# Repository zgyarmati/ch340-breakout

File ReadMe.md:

This a simple CH340G breakout board design, for using (mainly) on breadboards. There are a dozen of good designs out 
there, but this one tries to differentiate itself by being breadboard-friendly (meaning it’s possible to plug it into 
your board without sticking out vertically), provides (fused) power supply directly to the power rails of the breadboard 
(selectable 5V or 3V3), and it exposes all of the modem control lines.

 I decided to design this when I was starting prototyping an other project, and wished I had something similar. After a 
 quick, unsuccessful query on Tindie (this is something similar, but not designed for breadboard, and not OSHW), the 
 next thing I noticed was that I have Kicad open and I’m laying out this board. It’s nothing groundbreaking, but as you 
 can see on the pictures, it’s directly pluggable into breadboard, and it can also power your breadboard circuit from 
 the USB port, so I’m sure it can come handy sometimes to everyone on Earth. The schematic is pretty much the default 
 design for the CH340G chip, plus there is some ESD protection on the USB line (USBLC6-2SC6), a 3.3V regulator with 
 jumpers to select the output VCC and the UART line voltage and of course some LEDs for power and the TX/RX lines, as 
 blinking LEDs are mandatory for any reasonable gadget.

The PCB is designed with Kicad, it’s double sided, but possible to build it on single-sided board as well. You can find 
all of the CAD files in this repo, but  here is a teaser:

The usage it’s pretty straightforward: just plug it into your breadboard, connect the UART lines to your circuit, select 
the operating voltage, and connect the USB cable to your PC. If you are using any {r,d}ecent Linux distribution, the 
CH340G driver most likely is installed on your machine. If you are on Windows, you have to click around a bit, see for 
example the tutorial at Sparkfun 

Bookmarks
---------

http://nicecircuits.com/ch340g-usb-to-rs232-ttl-module-schematic-d-sun-v3-0/

https://www.tindie.com/products/bitluni/cam-prog/?utm_source=hackaday&utm_medium=link&utm_campaign=fromstore#specs

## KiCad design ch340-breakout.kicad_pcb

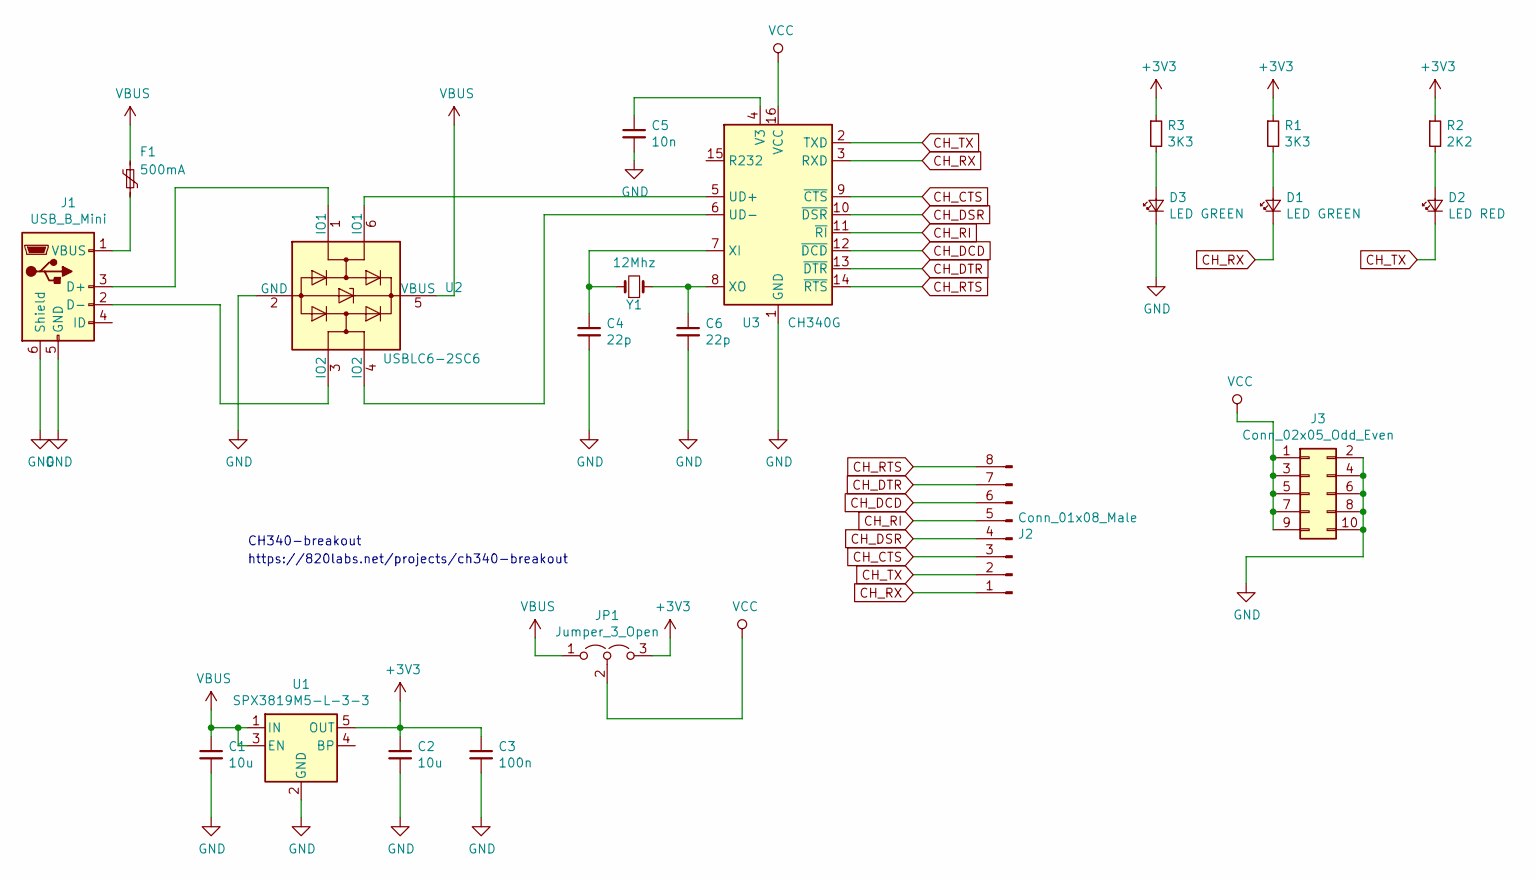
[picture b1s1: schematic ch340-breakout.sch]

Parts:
C1, C2: 10u; C_0805_2012Metric
C3: 100n; C_0805_2012Metric
C4, C6: 22p; C_0805_2012Metric
C5: 10n; C_0805_2012Metric
D1, D3: LED GREEN; LED_0805_2012Metric
D2: LED RED; LED_0805_2012Metric
F1: 500mA; Fuse_0805_2012Metric
J1: USB_B_Mini; USB_Mini-B_Lumberg_2486_01_Horizontal
J2: Conn_01x08_Male; PinHeader_1x08_P2.54mm_Vertical
J3: Conn_02x05_Odd_Even; PinHeader_2x05_P2.54mm_Vertical
JP1: Jumper_3_Open; PinHeader_1x03_P2.54mm_Vertical
R1, R3: 3K3; R_0805_2012Metric
R2: 2K2; R_0805_2012Metric
U1: SPX3819M5-L-3-3; SOT-23-5
U2: USBLC6-2SC6; SOT-23-6
U3: CH340G; SOIC-16_3.9x9.9mm_P1.27mm
Y1: 12Mhz; Crystal_SMD_HC49-SD

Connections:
+3V3: C2.1, C3.1, JP1.3 (B), R1.1, R2.1, R3.1, U1.5 (OUT)
CH_CTS: J2.3, U3.9 (~CTS)
CH_DCD: J2.6, U3.12 (~DCD)
CH_DSR: J2.4, U3.10 (~DSR)
CH_DTR: J2.7, U3.13 (~DTR)
CH_RI: J2.5, U3.11 (~RI)
CH_RTS: J2.8, U3.14 (~RTS)
CH_RX: D1.1 (K), J2.1, U3.3 (RXD)
CH_TX: D2.1 (K), J2.2, U3.2 (TXD)
GND: C1.2, C2.2, C3.2, C4.2, C5.2, C6.2, D3.1 (K), J1.5 (GND), J1.6 (Shield), J3.2, J3.4, J3.6, J3.8, J3.10, U1.2 (GND), U2.2 (GND), U3.1 (GND)
unnamed: C4.1, U3.7 (XI), Y1.1
unnamed: C5.1, U3.4 (V3)
unnamed: C6.1, U3.8 (XO), Y1.2
unnamed: D1.2 (A), R1.2
unnamed: D2.2 (A), R2.2
unnamed: D3.2 (A), R3.2
unnamed: F1.2, J1.1 (VBUS)
unnamed: J1.2 (D-), U2.3 (IO2)
unnamed: J1.3 (D+), U2.1 (IO1)
unnamed: U2.4 (IO2), U3.6 (UD-)
unnamed: U2.6 (IO1), U3.5 (UD+)
VBUS: C1.1, F1.1, JP1.1 (A), U1.1 (IN), U1.3 (EN), U2.5 (VBUS)
VCC: J3.1, J3.3, J3.5, J3.7, J3.9, JP1.2 (C), U3.16 (VCC)

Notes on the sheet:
CH340-breakout
https://820labs.net/projects/ch340-breakout

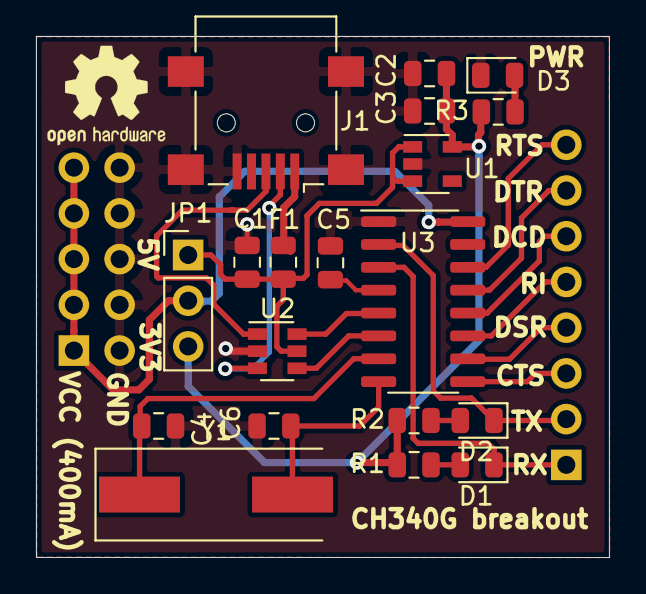
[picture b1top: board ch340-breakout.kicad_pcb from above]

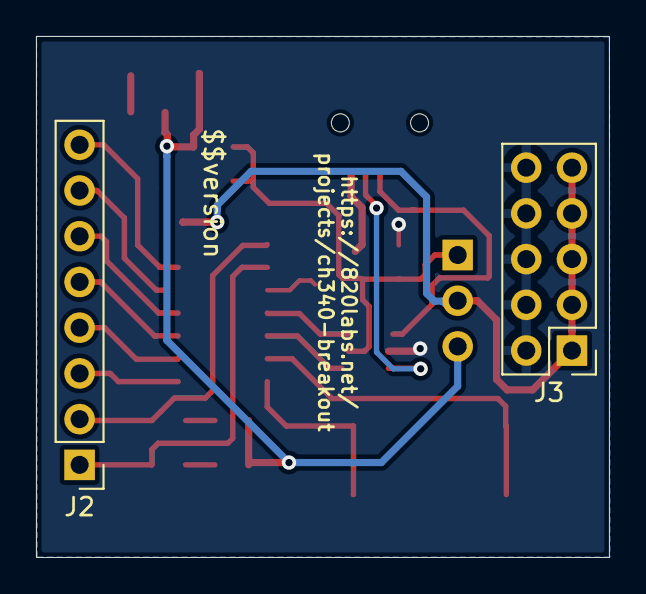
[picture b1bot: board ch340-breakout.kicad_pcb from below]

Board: 2 copper layers, 31.8 x 28.9 mm, 21 parts (2 on the bottom side), 23 nets.

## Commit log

2019-12-05 initial, empty repo
2019-12-05 test
2019-12-05 test2
2019-12-25 finalizing and add power on led
2019-12-26 silkscreen tweaks
2020-01-04 releasing rev1
2020-04-03 prepare for publishing: fixing LED resistor values, archive footprints, add missing data sheets
2020-04-04 add images and extend ReadMe
